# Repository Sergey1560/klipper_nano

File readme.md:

# Плата для подключения Klipper на NanoPi Neo Air к robin nano

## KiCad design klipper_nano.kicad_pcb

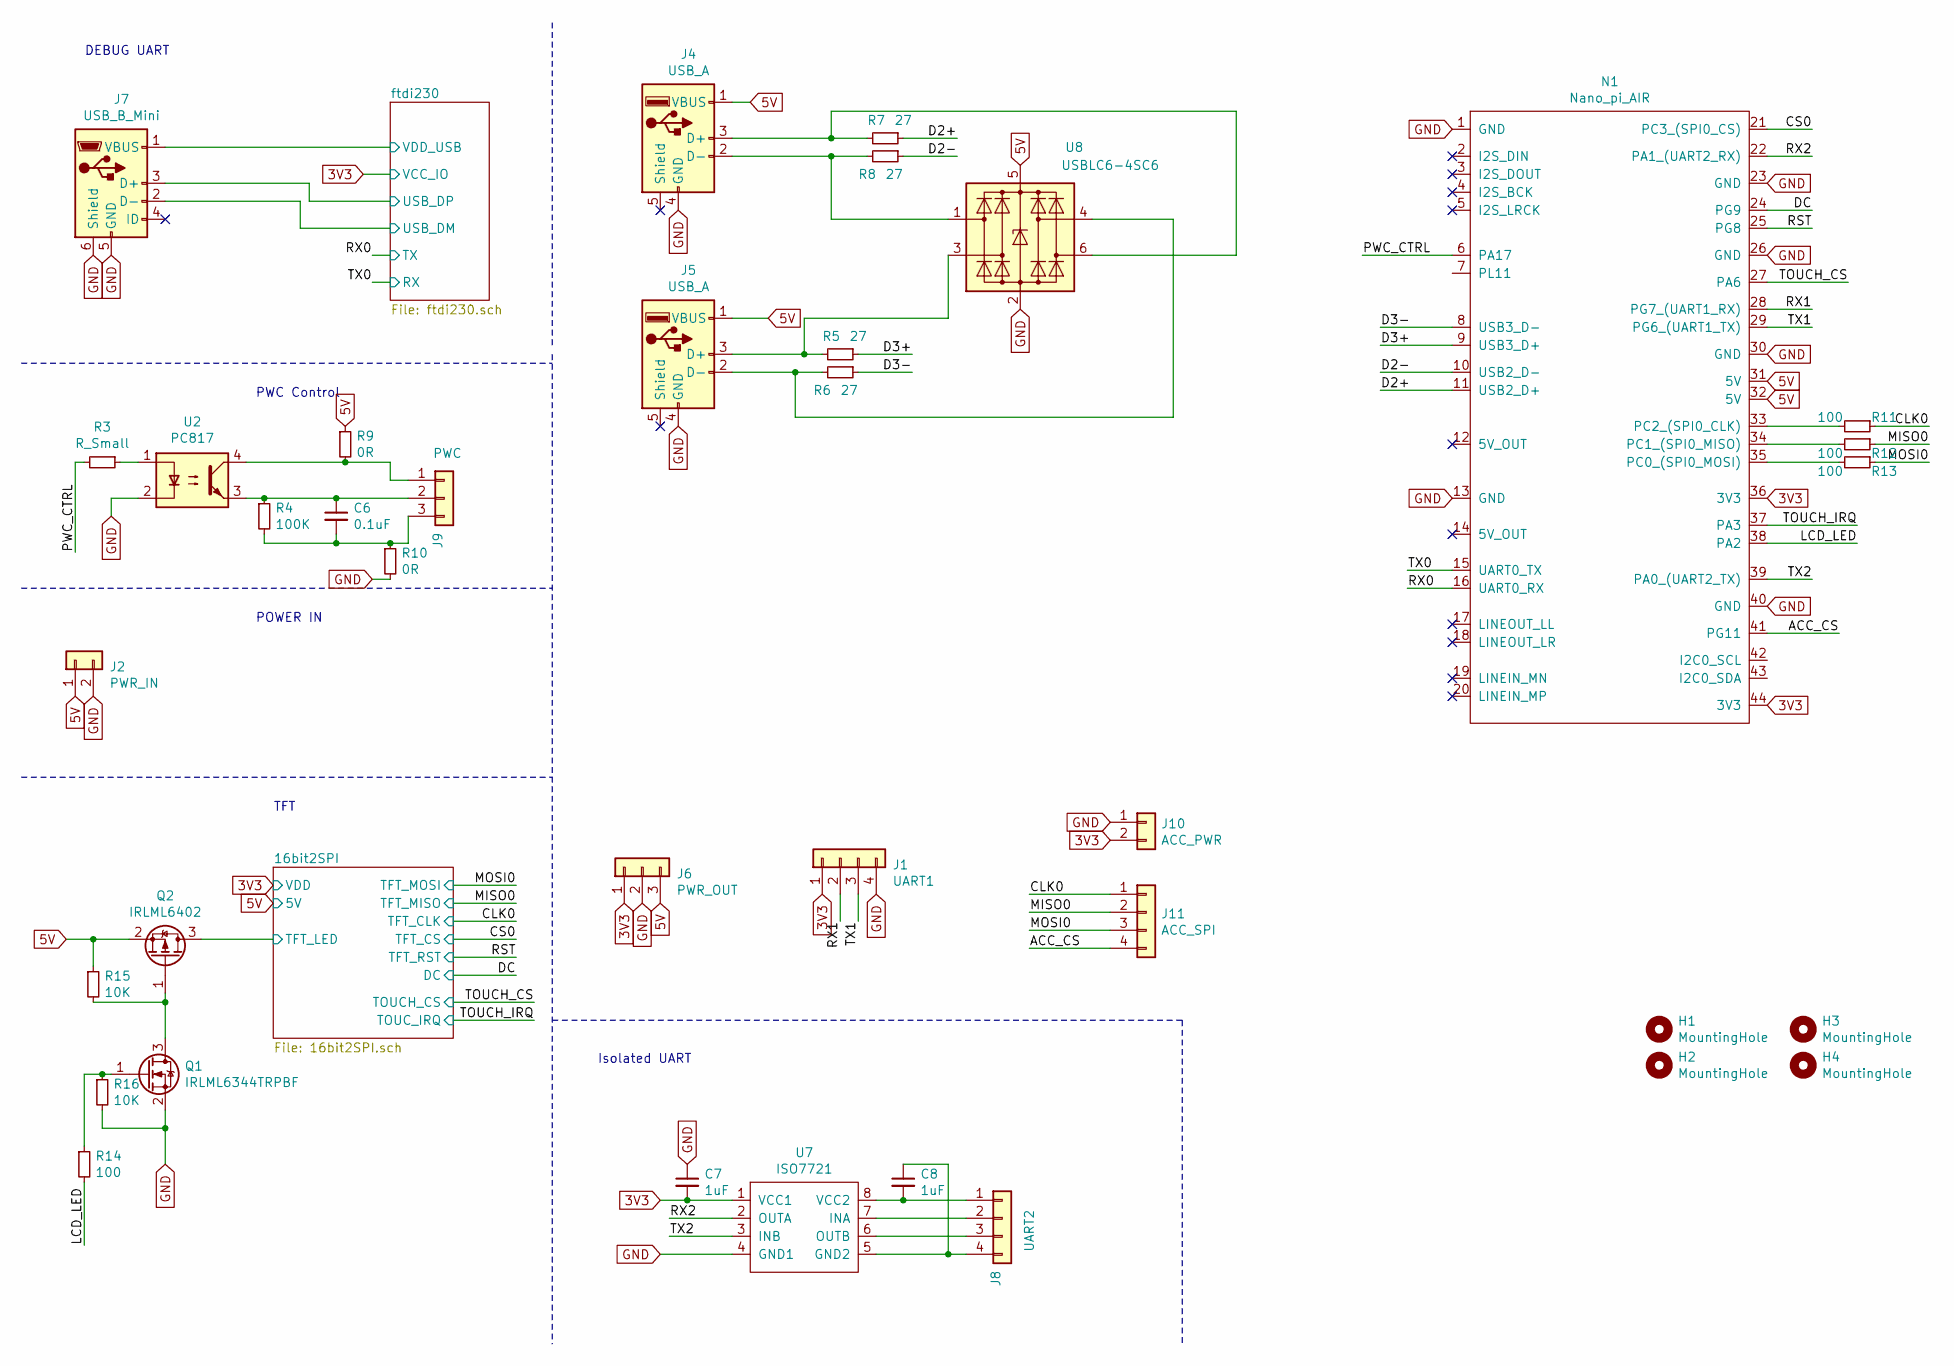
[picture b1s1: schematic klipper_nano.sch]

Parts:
C6: 0.1uF; C_0805_2012Metric
C7, C8: 1uF; C_0805_2012Metric
H1, H2, H3, H4: MountingHole; MountingHole_3.2mm_M3
J1: UART1; JST_XH_B4B-XH-A_1x04_P2.50mm_Vertical
J2: PWR_IN; JST_XH_B2B-XH-A_1x02_P2.50mm_Vertical
J4, J5: USB_A; USB_A_Molex_67643_Horizontal
J6: PWR_OUT; JST_XH_B3B-XH-A_1x03_P2.50mm_Vertical
J7: USB_B_Mini; USB_Mini-B_Wuerth_65100516121_Horizontal
J8: UART2; JST_XH_B4B-XH-A_1x04_P2.50mm_Vertical
J9: PWC; JST_XH_B3B-XH-A_1x03_P2.50mm_Vertical
J10: ACC_PWR; PinHeader_1x02_P2.54mm_Vertical
J11: ACC_SPI; PinHeader_1x04_P2.54mm_Vertical
N1: Nano_pi_AIR; nanopi_socket
Q1: IRLML6344TRPBF; SOT-23
Q2: IRLML6402; SOT-23
R3: R_Small; R_0805_2012Metric
R4: 100K; R_0805_2012Metric
R5, R6, R7, R8: 27; R_0805_2012Metric
R9, R10: 0R; R_0805_2012Metric
R11, R12, R13, R14: 100; R_0805_2012Metric
R15, R16: 10K; R_0805_2012Metric
U2: PC817; DIP-4_W7.62mm
U7: ISO7721; SOIC-8_3.9x4.9mm_P1.27mm
U8: USBLC6-4SC6; SOT-23-6

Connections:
3V3: C7.2, J1.1, J6.1, J10.2, N1.36 (3V3), N1.44 (3V3), U7.1 (VCC1); also elsewhere on the board
5V: J2.1, J4.1 (VBUS), J5.1 (VBUS), J6.3, N1.31 (5V), N1.32 (5V), Q2.2 (S), R9.1, R15.1, U8.5 (VBUS); also elsewhere on the board
/16bit2SPI/TFT_LED: Q2.3 (D); also elsewhere on the board
/ACC_CS: J11.4, N1.41 (PG11)
/CLK0: J11.1, R11.1; also elsewhere on the board
/CS0: N1.21 (PC3_(SPI0_CS)); also elsewhere on the board
/D2+: N1.11 (USB2_D+), R7.1
/D2-: N1.10 (USB2_D-), R8.1
/D3+: N1.9 (USB3_D+), R5.1
/D3-: N1.8 (USB3_D-), R6.1
/DC: N1.24 (PG9); also elsewhere on the board
/LCD_LED: N1.38 (PA2), R14.2
/MISO0: J11.2, R12.1; also elsewhere on the board
/MOSI0: J11.3, R13.1; also elsewhere on the board
/PWC_CTRL: N1.6 (PA17), R3.2
/RST: N1.25 (PG8); also elsewhere on the board
/RX0: N1.16 (UART0_RX); also elsewhere on the board
/RX1: J1.2, N1.28 (PG7_(UART1_RX))
/RX2: N1.22 (PA1_(UART2_RX)), U7.2 (OUTA)
/TOUCH_CS: N1.27 (PA6); also elsewhere on the board
/TOUCH_IRQ: N1.37 (PA3); also elsewhere on the board
/TX0: N1.15 (UART0_TX); also elsewhere on the board
/TX1: J1.3, N1.29 (PG6_(UART1_TX))
/TX2: N1.39 (PA0_(UART2_TX)), U7.3 (INB)
/ftdi230/USB_DM: J7.2 (D-); also elsewhere on the board
/ftdi230/USB_DP: J7.3 (D+); also elsewhere on the board
/ftdi230/VDD_USB: J7.1 (VBUS); also elsewhere on the board
GND: C7.1, J1.4, J2.2, J4.4 (GND), J5.4 (GND), J6.2, J7.5 (GND), J7.6 (Shield), J10.1, N1.1 (GND), N1.13 (GND), N1.23 (GND), N1.26 (GND), N1.30 (GND), N1.40 (GND), Q1.2 (S), R10.2, R16.2, U2.2, U7.4 (GND1), U8.2 (GND); also elsewhere on the board
unnamed: C6.1, J9.2, R4.1, U2.3
unnamed: C6.2, J9.3, R4.2, R10.1
unnamed: C8.1, J8.4, U7.5 (GND2)
unnamed: C8.2, J8.1, U7.8 (VCC2)
unnamed: J4.2 (D-), R8.2, U8.1 (I/O1)
unnamed: J4.3 (D+), R7.2, U8.6 (I/O4)
unnamed: J5.2 (D-), R6.2, U8.4 (I/O3)
unnamed: J5.3 (D+), R5.2, U8.3 (I/O2)
unnamed: J8.2, U7.7 (INA)
unnamed: J8.3, U7.6 (OUTB)
unnamed: J9.1, R9.2, U2.4
unnamed: N1.33 (PC2_(SPI0_CLK)), R11.2
unnamed: N1.34 (PC1_(SPI0_MISO)), R12.2
unnamed: N1.35 (PC0_(SPI0_MOSI)), R13.2
unnamed: Q1.1 (G), R14.1, R16.1
unnamed: Q1.3 (D), Q2.1 (G), R15.2
unnamed: R3.1, U2.1

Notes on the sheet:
DEBUG UART
PWC Control
POWER IN
TFT
Isolated UART

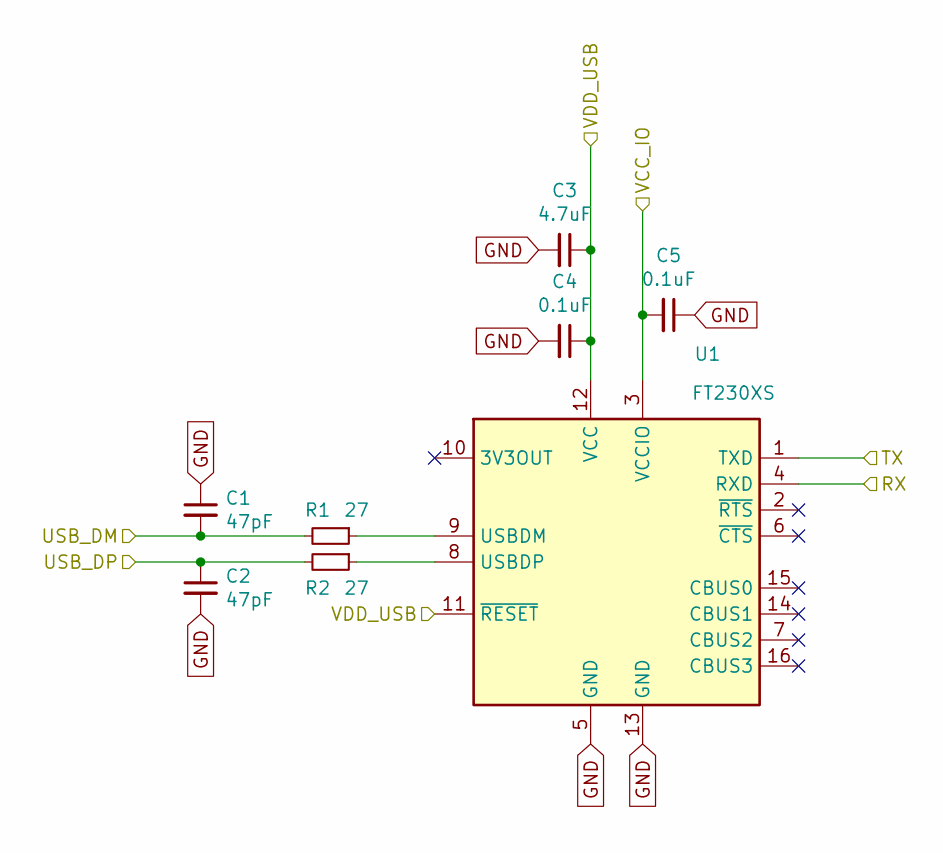
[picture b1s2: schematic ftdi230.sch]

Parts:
C1, C2: 47pF; C_0805_2012Metric
C3: 4.7uF; C_0805_2012Metric
C4, C5: 0.1uF; C_0805_2012Metric
R1, R2: 27; R_0805_2012Metric
U1: FT230XS; SSOP-16_3.9x4.9mm_P0.635mm

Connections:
3V3: C5.2, U1.3 (VCCIO); also elsewhere on the board
/RX0: U1.1 (TXD); also elsewhere on the board
/TX0: U1.4 (RXD); also elsewhere on the board
/ftdi230/USB_DM: C1.2, R1.2; also elsewhere on the board
/ftdi230/USB_DP: C2.1, R2.2; also elsewhere on the board
/ftdi230/VDD_USB: C3.1, C4.1, U1.11 (~RESET), U1.12 (VCC); also elsewhere on the board
GND: C1.1, C2.2, C3.2, C4.2, C5.1, U1.5 (GND), U1.13 (GND); also elsewhere on the board
unnamed: R1.1, U1.9 (USBDM)
unnamed: R2.1, U1.8 (USBDP)

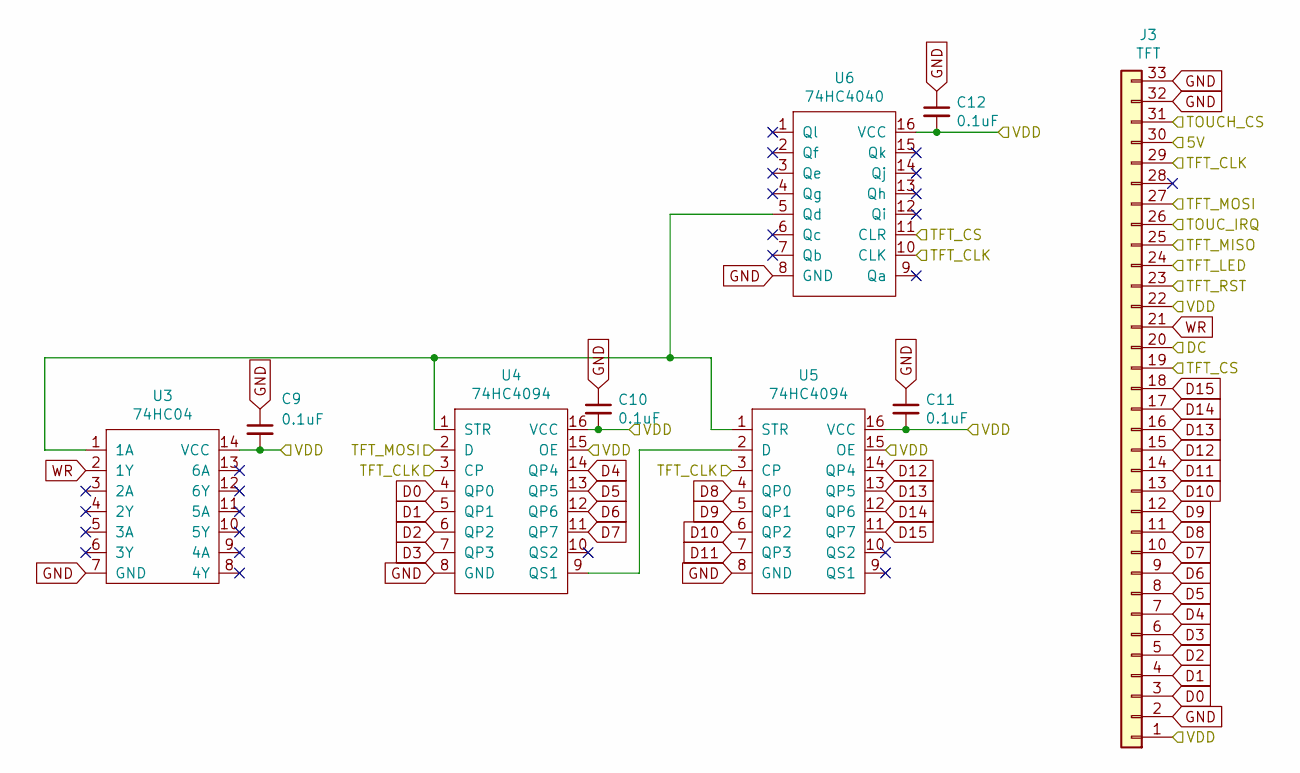
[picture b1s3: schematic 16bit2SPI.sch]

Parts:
C9, C10, C11, C12: 0.1uF; C_0805_2012Metric
J3: TFT; FPC32
U3: 74HC04; SOIC-14_3.9x8.7mm_P1.27mm
U4, U5: 74HC4094; SOIC-16_3.9x9.9mm_P1.27mm
U6: 74HC4040; SOIC-16_3.9x9.9mm_P1.27mm

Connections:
3V3: C9.2, C10.2, C11.2, C12.2, J3.1, J3.22, U3.14 (VCC), U4.15 (OE), U4.16 (VCC), U5.15 (OE), U5.16 (VCC), U6.16 (VCC); also elsewhere on the board
5V: J3.30; also elsewhere on the board
/16bit2SPI/TFT_LED: J3.24; also elsewhere on the board
/CLK0: J3.29, U4.3 (CP), U5.3 (CP), U6.10 (CLK); also elsewhere on the board
/CS0: J3.19, U6.11 (CLR); also elsewhere on the board
/DC: J3.20; also elsewhere on the board
/MISO0: J3.25; also elsewhere on the board
/MOSI0: J3.27, U4.2 (D); also elsewhere on the board
/RST: J3.23; also elsewhere on the board
/TOUCH_CS: J3.31; also elsewhere on the board
/TOUCH_IRQ: J3.26; also elsewhere on the board
D0: J3.3, U4.4 (QP0)
D1: J3.4, U4.5 (QP1)
D2: J3.5, U4.6 (QP2)
D3: J3.6, U4.7 (QP3)
D4: J3.7, U4.14 (QP4)
D5: J3.8, U4.13 (QP5)
D6: J3.9, U4.12 (QP6)
D7: J3.10, U4.11 (QP7)
D8: J3.11, U5.4 (QP0)
D9: J3.12, U5.5 (QP1)
D10: J3.13, U5.6 (QP2)
D11: J3.14, U5.7 (QP3)
D12: J3.15, U5.14 (QP4)
D13: J3.16, U5.13 (QP5)
D14: J3.17, U5.12 (QP6)
D15: J3.18, U5.11 (QP7)
GND: C9.1, C10.1, C11.1, C12.1, J3.2, J3.32, J3.33, U3.7 (GND), U4.8 (GND), U5.8 (GND), U6.8 (GND); also elsewhere on the board
unnamed: U3.1 (1A), U4.1 (STR), U5.1 (STR), U6.5 (Qd)
unnamed: U4.9 (QS1), U5.2 (D)
WR: J3.21, U3.2 (1Y)

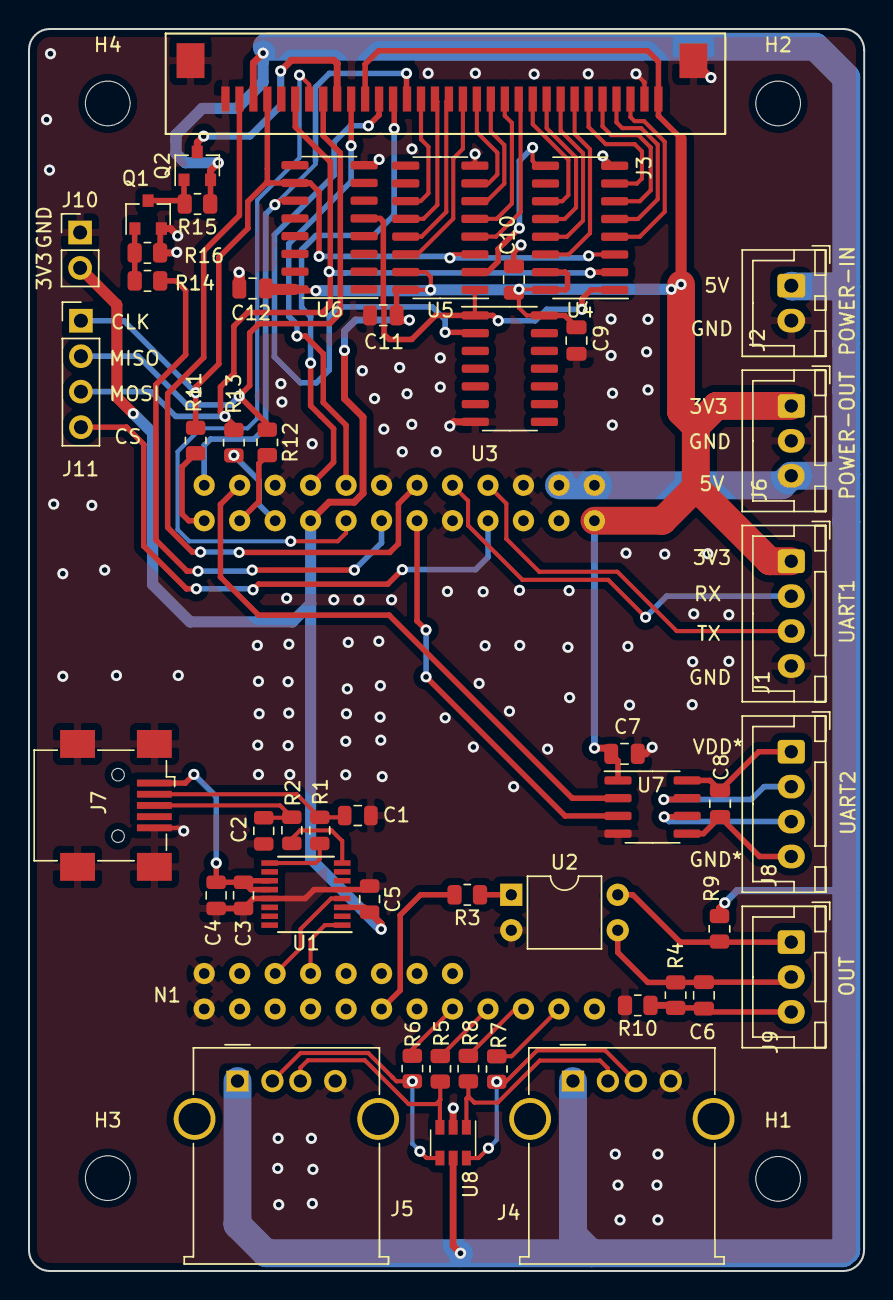
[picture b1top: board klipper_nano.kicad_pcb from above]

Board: 2 copper layers, 59.8 x 88.9 mm, 54 parts (0 on the bottom side), 66 nets.

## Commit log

2021-09-30 Initial
2021-09-30 readme
2021-09-30 Разъем под акселерометр Блок. конденсаторы Управление подстветкой экрана
